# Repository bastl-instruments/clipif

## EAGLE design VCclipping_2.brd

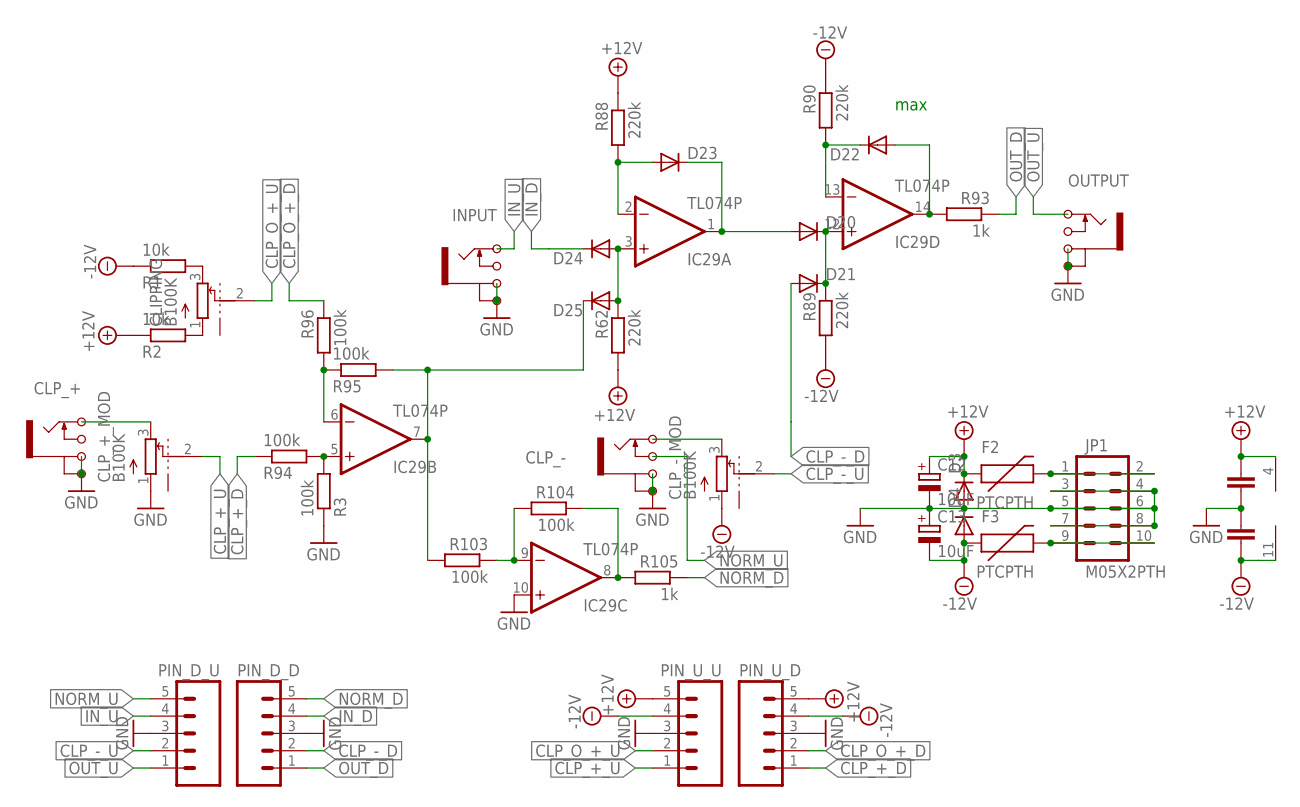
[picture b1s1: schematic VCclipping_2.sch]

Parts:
C6, C7: 100nF; C050-024X044
C12, C13: 10uF; E2,5-6E
CLIPPING: B100K; POT_ALPHA
CLP_+: JACK_MONOJACK_MONO; JACK_MONO
CLP_+_MOD: B100K; POT_ALPHA
CLP_-: JACK_MONOJACK_MONO; JACK_MONO
CLP_-_MOD: B100K; POT_ALPHA
D3, D4: DIODE-D-7.5; D-7.5
D20, D21, D22, D23, D24, D25: DIODE-D-5; D-5
F2, F3: PTCPTH; PTC
IC29: TL074P; DIL14
INPUT: JACK_MONOJACK_MONO; JACK_MONO
JP1: M05X2PTH; AVR_ICSP
OUTPUT: JACK_MONOJACK_MONO; JACK_MONO
PIN_D_D: M05PTH; 1X05
PIN_D_U: M05PTH; 1X05
PIN_U_D: M05PTH; 1X05
PIN_U_U: M05PTH; 1X05
R1, R2: 10k; 0204/5
R3, R94, R95, R96, R103, R104: 100k; 0204/5
R62, R88, R89, R90: 220k; 0204/5
R93, R105: 1k; 0204/5

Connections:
+12V: C6.2, C12.+, D3.C, F2.P$1 (1), IC29.4 (V+), PIN_U_D.5, PIN_U_U.5, R2.1, R62.2, R88.1
-12V: C7.1, C13.-, CLP_-_MOD.1, D4.A, F3.P$1 (1), IC29.11 (V-), PIN_U_D.4, PIN_U_U.4, R1.1, R89.2, R90.1
CLP_+_D: PIN_U_D.1, R94.1
CLP_+_U: CLP_+_MOD.2, PIN_U_U.1
CLP_-_D: D21.A, PIN_D_D.2
CLP_-_U: CLP_-_MOD.2, PIN_D_U.2
CLP_O_+_D: PIN_U_D.2, R96.1
CLP_O_+_U: CLIPPING.2, PIN_U_U.2
GND: C6.1, C7.2, C12.-, C13.+, CLP_+.G1, CLP_+.G2, CLP_+_MOD.1, CLP_-.G1, CLP_-.G2, D3.A, D4.C, IC29.10 (+IN), INPUT.G1, INPUT.G2, JP1.3, JP1.4, JP1.5, JP1.6, JP1.7, JP1.8, OUTPUT.G1, OUTPUT.G2, PIN_D_D.3, PIN_D_U.3, PIN_U_D.3, PIN_U_U.3, R3.1
IN_D: D24.C, PIN_D_D.4
IN_U: INPUT.T, PIN_D_U.4
unnamed: CLIPPING.3, R1.2
unnamed: CLIPPING.1, R2.2
unnamed: IC29.5 (+IN), R3.2, R94.2
unnamed: F2.P$2 (2), JP1.1, JP1.2
unnamed: F3.P$2 (2), JP1.9, JP1.10
unnamed: D24.A, D25.A, IC29.3 (+IN), R62.1
unnamed: D23.A, IC29.2 (-IN), R88.2
unnamed: D20.C, D21.C, IC29.12 (+IN), R89.1
unnamed: D22.C, IC29.13 (-IN), R90.2
unnamed: D22.A, IC29.14 (OUT), R93.2
unnamed: CLP_-.T, CLP_-_MOD.3
unnamed: D20.A, D23.C, IC29.1 (OUT)
unnamed: IC29.6 (-IN), R95.1, R96.2
unnamed: D25.C, IC29.7 (OUT), R95.2, R103.2
unnamed: CLP_+.T, CLP_+_MOD.3
unnamed: IC29.9 (-IN), R103.1, R104.2
unnamed: IC29.8 (OUT), R104.1, R105.2
NORM_D: PIN_D_D.5, R105.1
NORM_U: CLP_-.SW, PIN_D_U.5
OUT_D: PIN_D_D.1, R93.1
OUT_U: OUTPUT.T, PIN_D_U.1

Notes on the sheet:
max

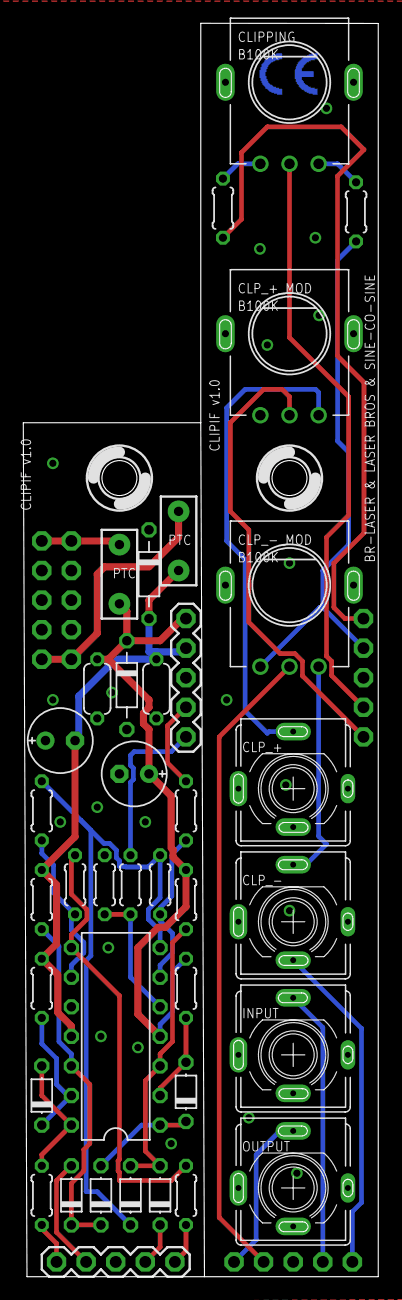
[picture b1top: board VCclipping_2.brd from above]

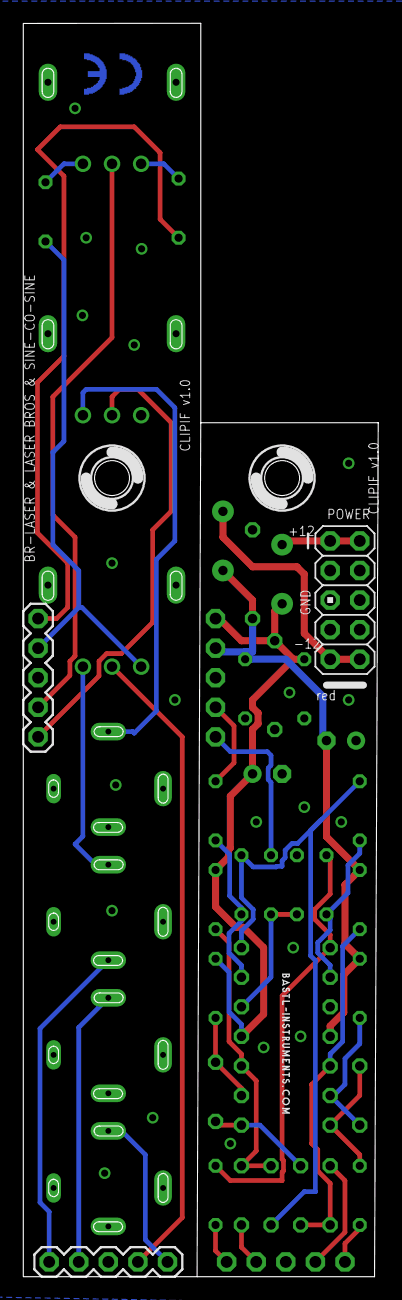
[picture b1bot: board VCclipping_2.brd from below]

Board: 2 copper layers, 30.5 x 107.6 mm, 45 parts (5 on the bottom side), 32 nets.

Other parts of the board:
U$1: CE_COPPER_4
U$4: BASTL_WEB_3
U$6, U$9: 3MM_HOLE

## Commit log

2021-08-09 added schematics
2021-08-09 added gerbers
2021-08-09 added expanded graphics + exports

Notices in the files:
parts and their libraries:
SparkFun-PowerIC: Licensing: Creative Commons ShareAlike 4.0 International - https://creativecommons.org/licenses/by-sa/4.0
